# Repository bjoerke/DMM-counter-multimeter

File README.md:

# DMM-counter-multimeter
Impulszähler und Multimeter für das DMM-Board

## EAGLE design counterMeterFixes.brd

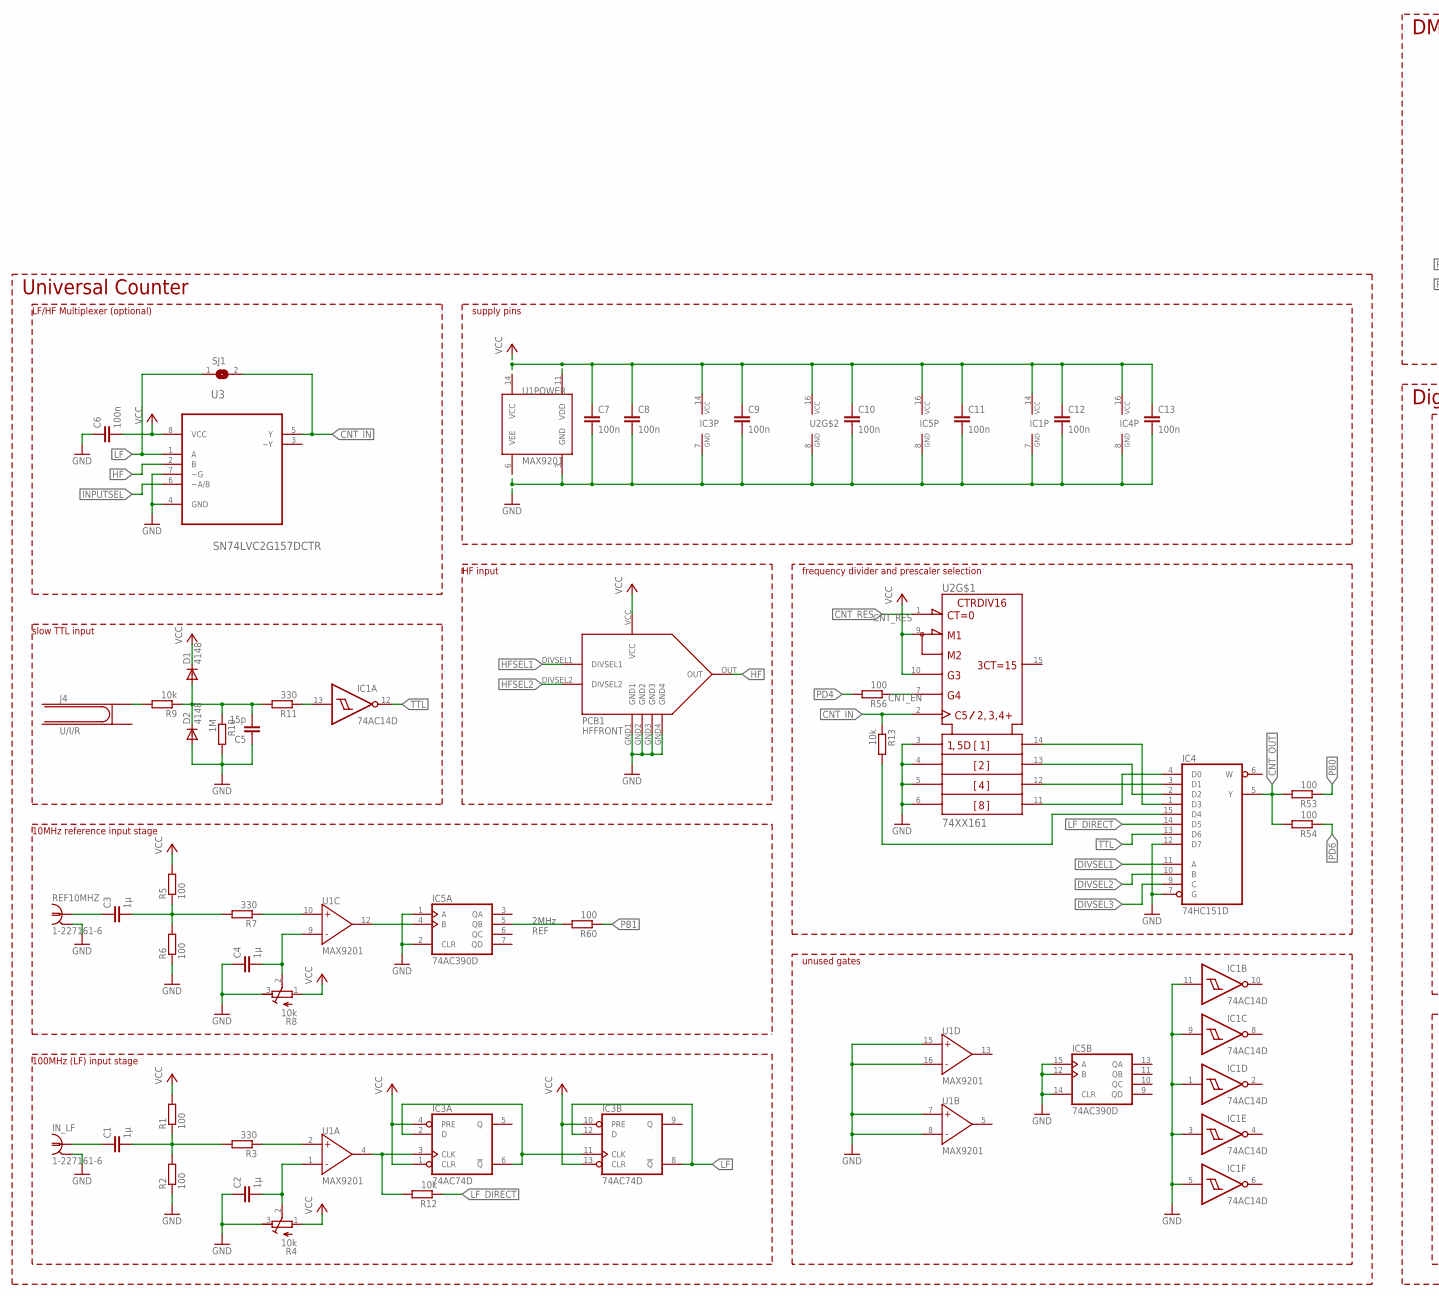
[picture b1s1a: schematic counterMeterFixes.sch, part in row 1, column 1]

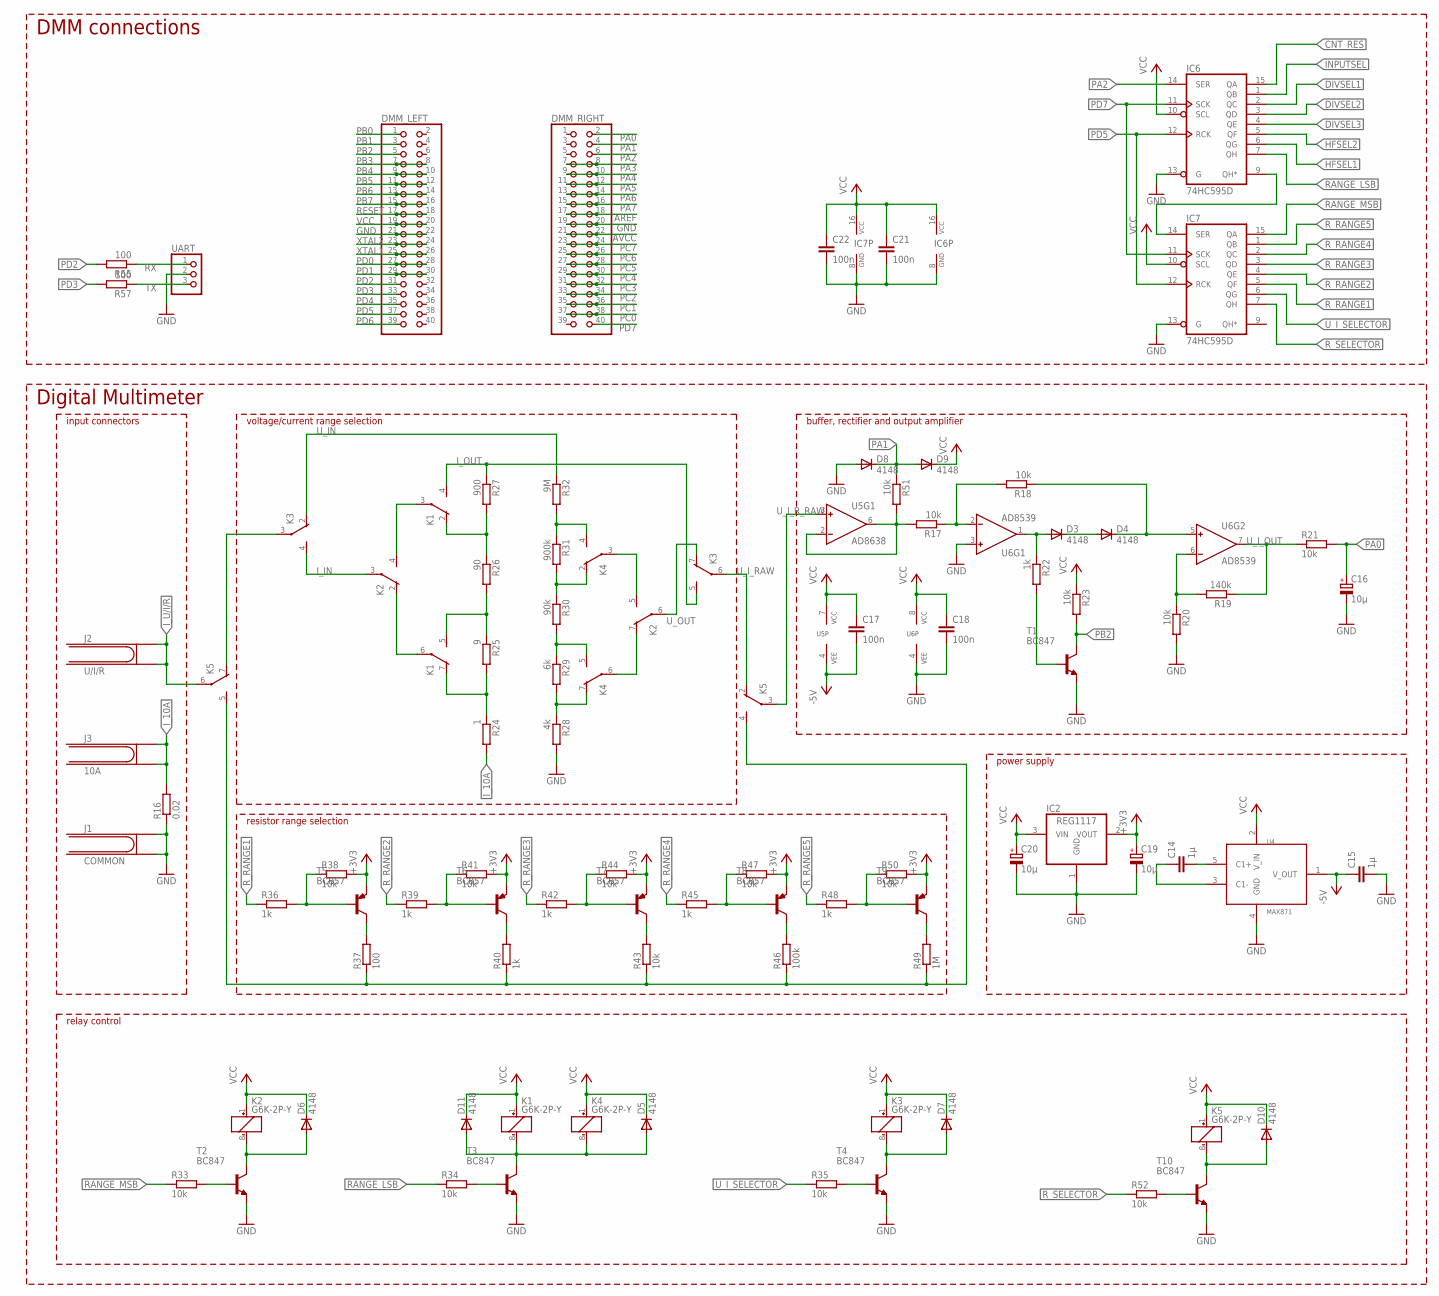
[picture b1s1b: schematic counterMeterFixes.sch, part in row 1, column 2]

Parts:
C1, C2, C3, C4, C14, C15: 1µ; C0603
C5: 15p; C0603
C6, C7, C8, C9, C10, C11, C12, C13, C17, C18, C21, C22: 100n; C0603
C16, C19, C20: 10µ; E2-5
D1, D2, D3, D4, D5, D6, D7, D8, D9, D10, D11: 4148; SOD323-W
DMM_LEFT: PINHD-2X20; 2X20
DMM_RIGHT: PINHD-2X20; 2X20
IC1: 74AC14D; SO14
IC2: REG1117; SOT223
IC3: 74AC74D; SO14
IC4: 74HC151D; SO16
IC5: 74AC390D; SO16
IC6, IC7: 74HC595D; SO16
IN_LF: 1-227161-6; AMP_227161
J1: COMMON; 4MMJACK
J2, J4: U/I/R; 4MMJACK
J3: 10A; 4MMJACK
K1, K2, K3, K4, K5: G6K-2P-Y
PCB1: HFFRONT
R1, R2, R5, R6, R37, R53, R54, R55, R56, R57, R60: 100; R0603
R3, R7, R11: 330; R0603
R4, R8: 10k; RTRIM64W
R9, R12, R13, R17, R18, R20, R21, R23, R33, R34, R35, R38, R41, R43, R44, R47, R50, R51, R52: 10k; R0603
R10, R49: 1M; R0603
R16: 0.02; R2512
R19: 140k; R0603
R22, R36, R39, R40, R42, R45, R48: 1k; R0603
R24: 1; R0603
R25: 9; R0603
R26: 90; R0603
R27: 900; R0603
R28: 4k; R0603
R29: 6k; R0603
R30: 90k; R0603
R31: 900k; R0603
R32: 9M; R0603
R46: 100k; R0603
REF10MHZ: 1-227161-6; AMP_227161
SJ1: SJ
T1, T2, T3, T4, T10: BC847; SOT23
T5, T6, T7, T8, T9: BC857; SOT23-BEC
U1: MAX9201; SOIC16
U2: 74XX161; SOIC16
U3: SN74LVC2G157DCTR; SOP65P400X130-8N
U4: MAX871; SOT23-5
U5: AD8638; SOIC8
U6: AD8539; SOIC8
UART: PINHD-1X3; 1X03

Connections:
+3V3: C19.+, IC2.2 (VOUT), R38.2, R41.2, R44.2, R47.2, R50.2, T5.E, T6.E, T7.E, T8.E, T9.E
-5V: C15.1, C17.2, U4.1 (V_OUT), U5.4 (VEE)
AREF: DMM_RIGHT.17, DMM_RIGHT.18
AVCC: DMM_RIGHT.21, DMM_RIGHT.22
CNT_EN: R56.1, U2.7 (ENP)
CNT_IN: R13.1, SJ1.2, U2.2 (CLK), U3.5 (Y)
CNT_IN_: IC4.15 (D4), R13.2
CNT_OUT: IC4.5 (Y), R53.2, R54.2
CNT_RES: IC6.15 (QA), U2.1 (!CLR)
DIVSEL1: IC4.11 (A), IC6.2 (QC)
DIVSEL2: IC4.10 (B), IC6.3 (QD)
DIVSEL3: IC4.9 (C), IC6.4 (QE)
GND: C2.1, C4.1, C5.1, C6.1, C7.2, C8.2, C9.2, C10.2, C11.2, C12.2, C13.2, C15.2, C16.-, C18.2, C19.-, C20.-, C21.2, C22.2, D2.A, D8.A, DMM_LEFT.21, DMM_LEFT.22, DMM_RIGHT.19, DMM_RIGHT.20, IC1.1 (I), IC1.3 (I), IC1.5 (I), IC1.7 (GND), IC1.9 (I), IC1.11 (I), IC2.1 (GND), IC3.7 (GND), IC4.7 (G), IC4.8 (GND), IC4.12 (D7), IC5.1 (A), IC5.2 (CLR), IC5.8 (GND), IC5.12 (B), IC5.14 (CLR), IC5.15 (A), IC6.8 (GND), IC6.13 (G), IC7.8 (GND), IC7.13 (G), IN_LF.2, J1.1@1 (1), J1.1@2 (2), PCB1.GND1, PCB1.GND2, PCB1.GND3, PCB1.GND4, R2.1, R4.3 (A), R6.1, R8.3 (A), R10.2, R16.1, R20.2, R28.2, REF10MHZ.2, T1.2 (E), T2.2 (E), T3.2 (E), T4.2 (E), T10.2 (E), U1.3 (GND), U1.6 (VEE), U1.7 (IN+), U1.8 (IN-), U1.15 (IN+), U1.16 (IN-), U2.3 (A), U2.4 (B), U2.5 (C), U2.6 (D), U2.8 (GND), U3.4 (GND), U3.7 (~G), U4.4 (GND), U6.3 (IN+), U6.4 (VEE), UART.2
HF: PCB1.OUT, U3.2 (B)
HFSEL1: IC6.6 (QG), PCB1.DIVSEL1
HFSEL2: IC6.5 (QF), PCB1.DIVSEL2
INPUTSEL: IC6.1 (QB), U3.6 (~A/B)
I_10A: J3.1@1 (1), J3.1@2 (2), R16.2, R24.2
I_IN: K2.3, K3.4 (S)
I_OUT: K1.4 (S), K3.5 (S), R27.1
I_U/I/R: J2.1@1 (1), J2.1@2 (2), K5.6
LF: IC3.8 (!Q), IC3.12 (D), SJ1.1, U3.1 (A)
LF_DIRECT: IC4.14 (D5), R12.1
LF_SIG: IC3.3 (CLK), R12.2, U1.4 (OUT)
unnamed: C2.2, R4.2 (S), U1.1 (IN-)
unnamed: R3.1, U1.2 (IN+)
unnamed: C1.2, R1.1, R2.2, R3.2
unnamed: C1.1, IN_LF.1
unnamed: C4.2, R8.2 (S), U1.9 (IN-)
unnamed: R7.1, U1.10 (IN+)
unnamed: C3.2, R5.1, R6.2, R7.2
unnamed: C3.1, REF10MHZ.1
unnamed: J4.1@1 (1), R9.2
unnamed: C5.2, D1.A, D2.C, R9.1, R10.1, R11.2
unnamed: IC1.13 (I), R11.1
unnamed: K4.7 (O), R28.1, R29.2
unnamed: IC5.4 (B), U1.12 (OUT)
unnamed: IC4.1 (D3), U2.14 (QA)
unnamed: K1.3, K2.4 (S)
unnamed: IC4.2 (D2), U2.13 (QB)
unnamed: IC4.3 (D1), U2.12 (QC)
unnamed: IC4.4 (D0), U2.11 (QD)
unnamed: C14.2, U4.5 (C1+)
unnamed: C14.1, U4.3 (C1-)
unnamed: D3.A, R22.1, U6.1 (OUT)
unnamed: D4.C, R18.1, U6.5 (IN+)
unnamed: R19.2, R20.1, U6.6 (IN-)
unnamed: IC6.9 (QH*), IC7.14 (SER)
unnamed: R17.1, R18.2, U6.2 (IN-)
unnamed: R17.2, R51.2, U5.2 (IN-), U5.6 (OUT)
unnamed: D3.C, D4.A
unnamed: R22.2, T1.1 (B)
unnamed: K1.7 (O), R24.1, R25.2
unnamed: K1.5 (S), R25.1, R26.2
unnamed: K1.2 (O), R26.1, R27.2
unnamed: K1.6, K2.2 (O)
unnamed: K4.5 (S), R29.1, R30.2
unnamed: K4.2 (O), R30.1, R31.2
unnamed: K4.4 (S), R31.1, R32.2
unnamed: K2.5 (S), K4.3
unnamed: K2.7 (O), K4.6
unnamed: D6.A, K2.8 (-), T2.3 (C)
unnamed: R33.2, T2.1 (B)
unnamed: D5.A, D11.A, K1.8 (-), K4.8 (-), T3.3 (C)
unnamed: R34.2, T3.1 (B)
unnamed: R35.2, T4.1 (B)
unnamed: D7.A, K3.8 (-), T4.3 (C)
unnamed: R36.2, R38.1, T5.B
unnamed: R37.2, T5.C
unnamed: K3.3, K5.7 (O)
unnamed: IC3.2 (D), IC3.6 (!Q), IC3.11 (CLK)
unnamed: R39.2, R41.1, T6.B
unnamed: R40.2, T6.C
unnamed: R42.2, R44.1, T7.B
unnamed: R43.2, T7.C
unnamed: R45.2, R47.1, T8.B
unnamed: R46.2, T8.C
unnamed: R48.2, R50.1, T9.B
unnamed: R49.2, T9.C
unnamed: K5.4 (S), K5.5 (S), R37.1, R40.1, R43.1, R46.1, R49.1
unnamed: R52.2, T10.1 (B)
unnamed: D10.A, K5.8 (-), T10.3 (C)
PA0: C16.+, DMM_RIGHT.2, R21.2
PA1: D8.C, D9.A, DMM_RIGHT.4, R51.1
PA2: DMM_RIGHT.6, IC6.14 (SER)
PA3: DMM_RIGHT.7, DMM_RIGHT.8
PA4: DMM_RIGHT.9, DMM_RIGHT.10
PA5: DMM_RIGHT.11, DMM_RIGHT.12
PA6: DMM_RIGHT.13, DMM_RIGHT.14
PA7: DMM_RIGHT.15, DMM_RIGHT.16
PB0: DMM_LEFT.1, R53.1
PB1: DMM_LEFT.3, R60.1
PB2: DMM_LEFT.5, R23.2, T1.3 (C)
PB3: DMM_LEFT.7, DMM_LEFT.8
PB4: DMM_LEFT.9, DMM_LEFT.10
PB5: DMM_LEFT.11, DMM_LEFT.12
PB6: DMM_LEFT.13, DMM_LEFT.14
PB7: DMM_LEFT.15, DMM_LEFT.16
PC0: DMM_RIGHT.37, DMM_RIGHT.38
PC1: DMM_RIGHT.35, DMM_RIGHT.36
PC2: DMM_RIGHT.33, DMM_RIGHT.34
PC3: DMM_RIGHT.31, DMM_RIGHT.32
PC4: DMM_RIGHT.29, DMM_RIGHT.30
PC5: DMM_RIGHT.27, DMM_RIGHT.28
PC6: DMM_RIGHT.25, DMM_RIGHT.26
PC7: DMM_RIGHT.23, DMM_RIGHT.24
PD0: DMM_LEFT.27, DMM_LEFT.28
PD1: DMM_LEFT.29, DMM_LEFT.30
PD2: DMM_LEFT.31, R55.2
PD3: DMM_LEFT.33, R57.2
PD4: DMM_LEFT.35, R56.2
PD5: DMM_LEFT.37, IC6.12 (RCK), IC7.12 (RCK)
PD6: DMM_LEFT.39, R54.1
PD7: DMM_RIGHT.40, IC6.11 (SCK), IC7.11 (SCK)
RANGE_LSB: IC6.7 (QH), R34.1
RANGE_MSB: IC7.15 (QA), R33.1
REF: IC5.5 (QB), R60.2
RESET: DMM_LEFT.17, DMM_LEFT.18
RX: R55.1, UART.1
R_RANGE1: IC7.5 (QF), R36.1
R_RANGE2: IC7.4 (QE), R39.1
R_RANGE3: IC7.3 (QD), R42.1
R_RANGE4: IC7.2 (QC), R45.1
R_RANGE5: IC7.1 (QB), R48.1
R_SELECTOR: IC7.7 (QH), R52.1
TTL: IC1.12 (O), IC4.13 (D6)
TX: R57.1, UART.3
U_IN: K3.2 (O), R32.1
U_I_OUT: R19.1, R21.1, U6.7 (OUT)
U_I_RAW: K3.6, K5.2 (O)
U_I_R_RAW: K5.3, U5.3 (IN+)
U_I_SELECTOR: IC7.6 (QG), R35.1
U_OUT: K2.6, K3.7 (O)
VCC: C6.2, C7.1, C8.1, C9.1, C10.1, C11.1, C12.1, C13.1, C17.1, C18.1, C20.+, C21.1, C22.1, D1.C, D5.C, D6.C, D7.C, D9.C, D10.C, D11.C, DMM_LEFT.19, DMM_LEFT.20, IC1.14 (VCC), IC2.3 (VIN), IC3.1 (CLR), IC3.4 (PRE), IC3.10 (PRE), IC3.13 (CLR), IC3.14 (VCC), IC4.16 (VCC), IC5.16 (VCC), IC6.10 (SCL), IC6.16 (VCC), IC7.10 (SCL), IC7.16 (VCC), K1.1 (+), K2.1 (+), K3.1 (+), K4.1 (+), K5.1 (+), PCB1.VCC, R1.2, R4.1 (E), R5.2, R8.1 (E), R23.1, U1.11 (VDD), U1.14 (VCC), U2.9 (!LOAD), U2.10 (ENT), U2.16 (VCC), U3.8 (VCC), U4.2 (V_IN), U5.7 (VCC), U6.8 (VCC)
XTAL1: DMM_LEFT.25, DMM_LEFT.26
XTAL2: DMM_LEFT.23, DMM_LEFT.24

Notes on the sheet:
10MHz reference input stage
HF input
slow TTL input
100MHz (LF) input stage
LF/HF Multiplexer (optional)
2MHz
supply pins
frequency divider and prescaler selection
unused gates
Universal Counter
relay control
resistor range selection
voltage/current range selection
buffer, rectifier and output amplifier
input connectors
power supply
Digital Multimeter
DMM connections

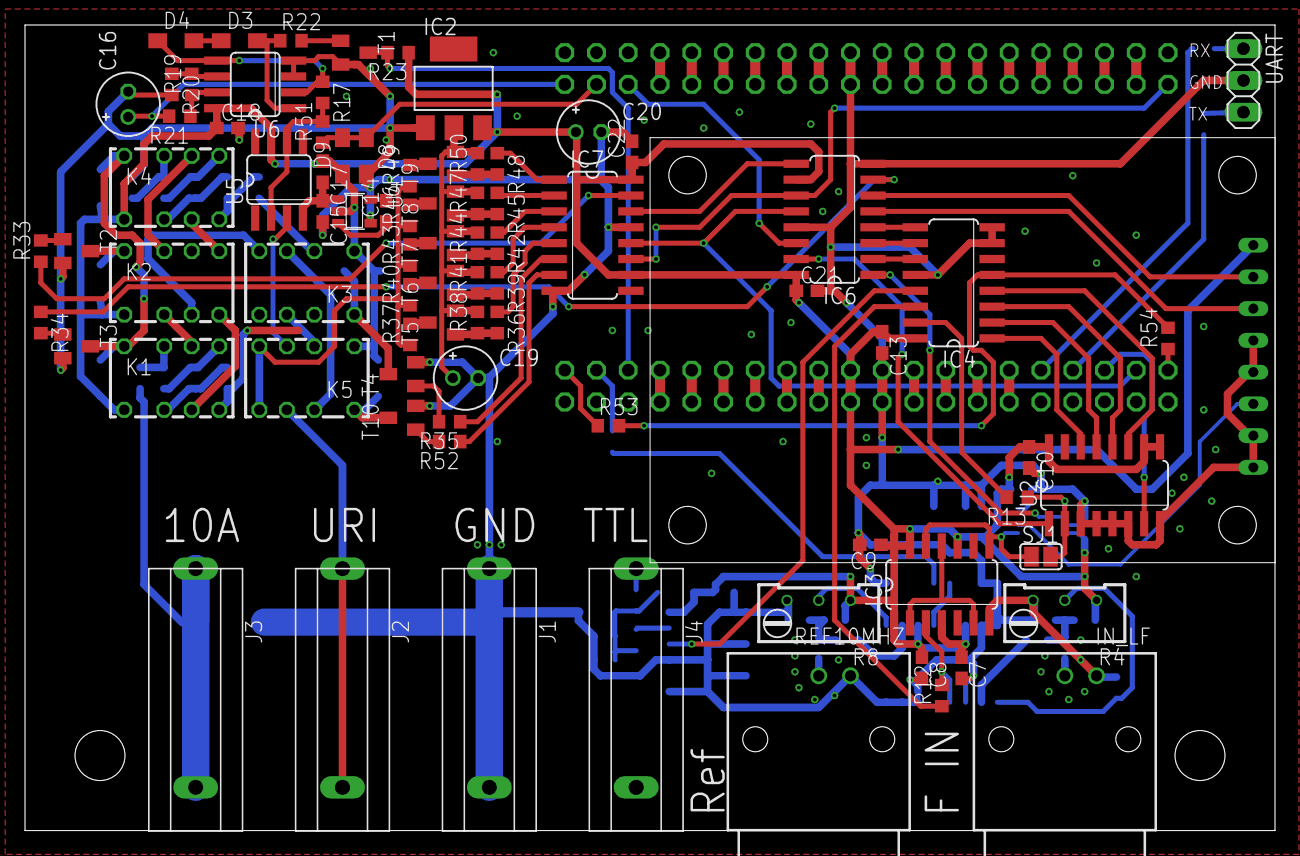
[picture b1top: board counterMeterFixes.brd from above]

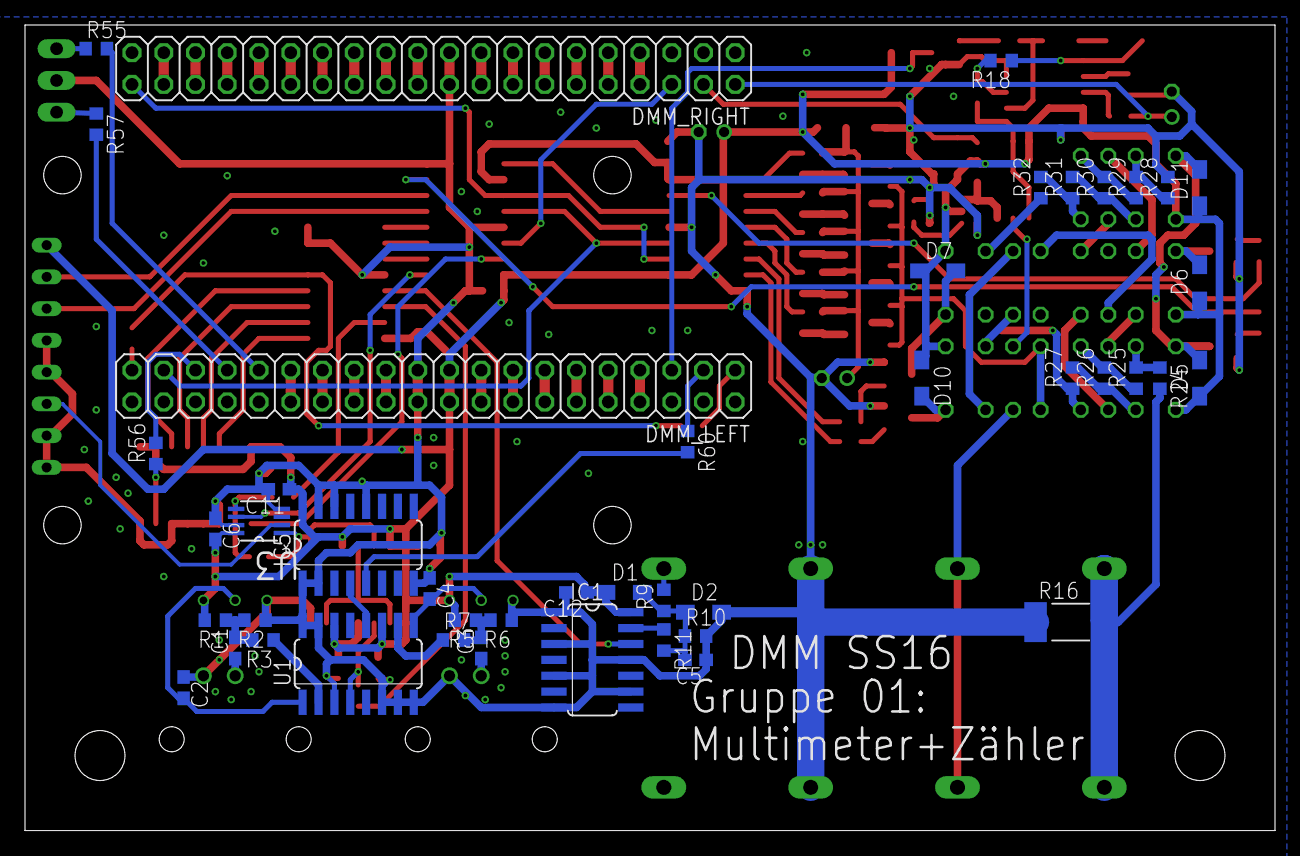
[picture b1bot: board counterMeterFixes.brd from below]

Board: 2 copper layers, 100.0 x 64.4 mm, 128 parts (45 on the bottom side), 136 nets.

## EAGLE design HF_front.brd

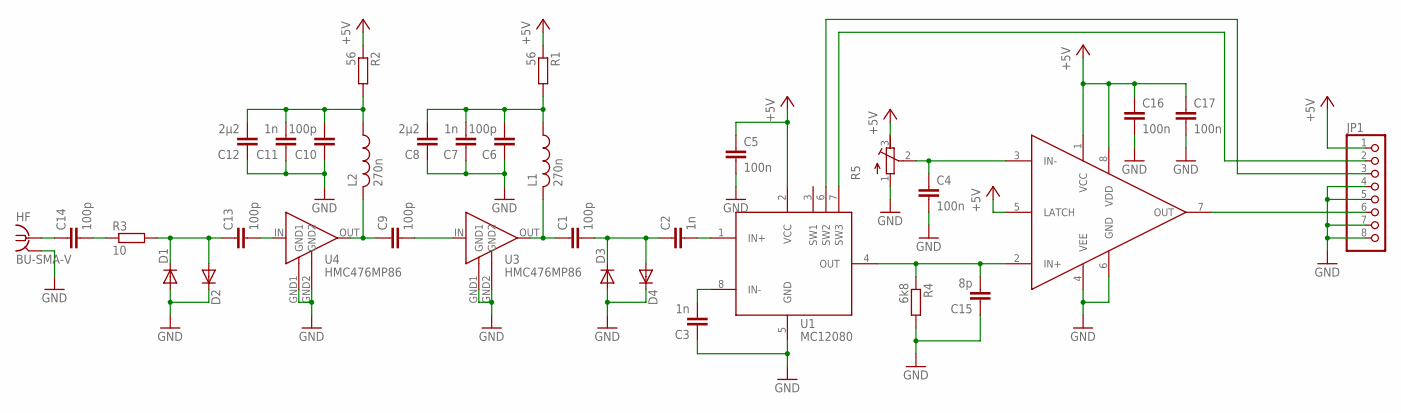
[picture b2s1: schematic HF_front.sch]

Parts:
C1, C6, C9, C10, C13, C14: 100p; C0603
C2, C3, C7, C11: 1n; C0603
C4, C5, C16, C17: 100n; C0603
C8, C12: 2µ2; C0603
C15: 8p; C0603
D1, D2, D3, D4: DIODE-SOD323-W; SOD323-W
HF: BU-SMA-V
JP1: PINHD-1X8; 1X08
L1, L2: 270n; R0603
R1, R2: 56; R0603
R3: 10; R0603
R4: 6k8; R0603
R5: R-TRIMM64W; RTRIM64W
U1: MC12080; SOIC8
U2: MAX9203; SOIC8
U3, U4: HMC476MP86; MICRO-X

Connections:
+5V: C5.1, C16.1, C17.1, JP1.1, R1.1, R2.1, R5.3 (A), U1.2 (VCC), U2.1 (VCC), U2.5 (LATCH), U2.8 (VDD)
GND: C3.1, C4.2, C5.2, C6.1, C7.1, C8.1, C10.1, C11.1, C12.1, C15.1, C16.2, C17.2, D1.A, D2.C, D3.A, D4.C, HF.2, HF.3 (2), HF.4 (2), HF.5 (2), JP1.4, JP1.5, JP1.7, JP1.8, R4.2, R5.1 (E), U1.5 (GND), U2.4 (VEE), U2.6 (GND), U3.GND1, U3.GND2, U4.GND1, U4.GND2
unnamed: C6.2, C7.2, C8.2, L1.1, R1.2
unnamed: C1.1, L1.2, U3.OUT
unnamed: C10.2, C11.2, C12.2, L2.1, R2.2
unnamed: C9.1, L2.2, U4.OUT
unnamed: C9.2, U3.IN
unnamed: C2.2, U1.1 (IN+)
unnamed: C3.2, U1.8 (IN-)
unnamed: C15.2, R4.1, U1.4 (OUT), U2.2 (IN+)
unnamed: C4.1, R5.2 (S), U2.3 (IN-)
unnamed: C14.1, HF.1
unnamed: C14.2, R3.1
unnamed: C13.1, D1.C, D2.A, R3.2
unnamed: C13.2, U4.IN
unnamed: C1.2, C2.1, D3.C, D4.A
unnamed: JP1.6, U2.7 (OUT)
unnamed: JP1.2, U1.7 (SW3)
unnamed: JP1.3, U1.6 (SW2)

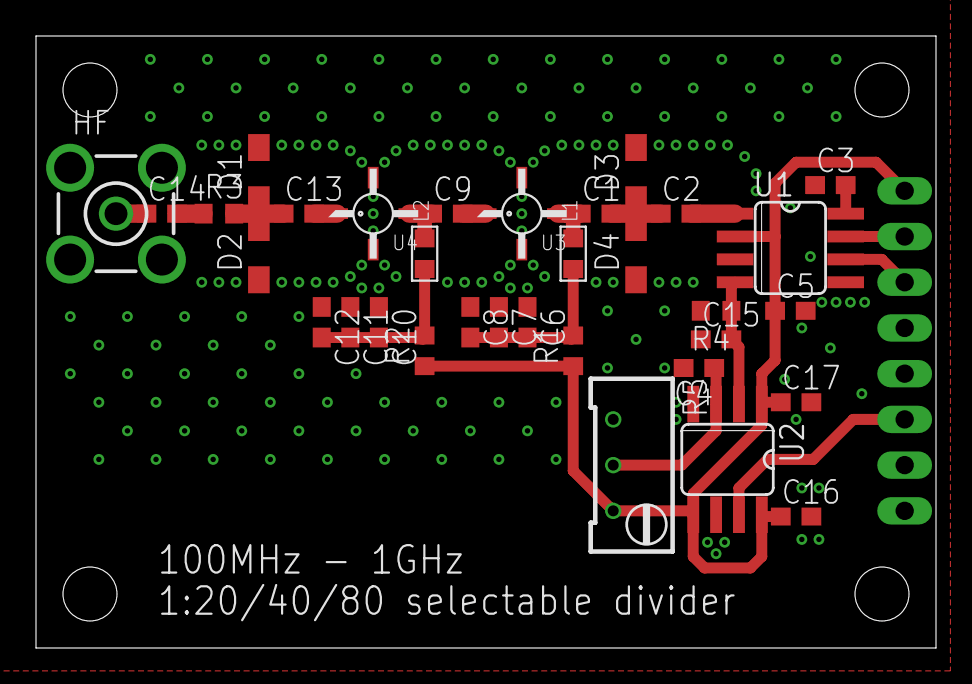
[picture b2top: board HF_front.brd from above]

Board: 2 copper layers, 50.0 x 34.0 mm, 34 parts (1 on the bottom side), 19 nets.

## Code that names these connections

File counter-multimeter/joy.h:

#ifndef _JOY_H_
#define _JOY_H_

#include <avr/io.h>
#include <avr/interrupt.h>
#include <stdint.h>
#include <stdlib.h>
#include <util/delay.h>
#include <avr/pgmspace.h>
#include <avr/wdt.h>

#include "systime.h"
#include "gui.h"

#define JOY_PIN			PINA
#define JOY_DDR			DDRA
#define JOY_PORT		PORTA

#define JOY_UP_PIN		PA7
#define JOY_RIGHT_PIN 	PA4
#define JOY_DOWN_PIN	PA6
#define JOY_LEFT_PIN	PA5
#define JOY_PUSH_PIN	PA3

#define JOY_MASK 		((1<<JOY_UP_PIN)|(1<<JOY_RIGHT_PIN)|(1<<JOY_DOWN_PIN)|(1<<JOY_LEFT_PIN)|(1<<JOY_PUSH_PIN))

#define JOY_UP			0x80
#define JOY_RIGHT		0x10
#define JOY_DOWN		0x40
#define JOY_LEFT		0x20
#define JOY_PUSH		0x08

struct {
	uint8_t state;
	uint8_t pressed;
} joy;

/**
 * \brief Initializes joystick
 */
void joy_Init(void);

/**
 * \brief Reports if a joystick button has been pressed
 *
 * Each press is only reported once.
 *
 * \param joymask Joystick button that will be checked.
 * \return Mask of pressed buttons
 */
uint8_t joy_Pressed(uint8_t joymask);

/**
 * \brief Reports if a joystick button is currently pressed
 *
 * \param joymask Joystick button that will be checked.
 * \return Mask of pressed buttons
 */
uint8_t joy_State(uint8_t joymask);

/**
 *  \brief Reads joystick pins, debounces and writes new state
 *
 *  see: https://www.mikrocontroller.net/articles/Entprellung
 */
void joy_Update(void);

#endif

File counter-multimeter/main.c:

#ifndef F_CPU
#define F_CPU 16000000UL
#endif

#include <avr/io.h>
#include <avr/interrupt.h>
#include <stdint.h>
#include <stdlib.h>
#include <avr/pgmspace.h>

#include "uartProtocol.h"
#include "includes/lcd.h"
#include "includes/twi.h"
#include "multimeter.h"
#include "systime.h"
#include "counterHAL.h"
#include "gui.h"
#include "joy.h"

int main(void) {
	//// set PB0-PB3 as output
	//DDRB = 0x0F;
	//// set PB0-PB3 on high-level (internal Pull-Up on)
	//PORTB |= 0x0F;		// Required for DMM Board DMM Board 2013

	// set PB0, PB1, PB3 as output
	DDRB = 0x0B;		// 1011
	// set PB0, PB1, PB3 on high-level (internal Pull-Up on)
	PORTB |= 0x0B;		// Required for DMM Board DMM Board 2013
	// set PB2 as input
	DDRB &= ~(1 << PINB2);
	// set PB2 on high-level (internal Pull-Up on)
	PORTB |= (1 << PINB2);

	LCD_Init();
	uartProtocol_Init();

	time_Init();
	joy_Init();
	shift_Init();
	counter_Init();
	ADC_Init();

	Backlight_LED(BL_BLUE_ON | BL_GREEN_ON | BL_RED_ON);

	LCD_Clear();
/*	LCD_PutString_P(PSTR("	                   \r\n"));
	LCD_PutString_P(PSTR("	                   \r\n"));
	LCD_PutString_P(PSTR("    Willkommen zur   \r\n"));
	LCD_PutString_P(PSTR("     Demo-Version    \r\n"));
	LCD_PutString_P(PSTR("         des         \r\n"));
	LCD_PutString_P(PSTR("    Counter-Meters   \r\n"));
	LCD_PutString_P(PSTR("                     \r\n"));
	LCD_PutString_P(PSTR("                     \r\n")); */
	LCD_Update();
	//time_Waitms(3000);

	// Enable interrupts:
	sei();

/*
    //UART protocol ussage
	uint8_t i=0;
	while(1) {
		request* request = 
		uartProtocol_WaitRequest();
		LCD_PutString("#");
		LCD_Update();
		response response;
		response.direct_voltage.range = i;
		response.direct_voltage.value = 0;
		uartProtocol_SendResponse(&response);
		i++;
	} 
*/
	
	while (1) {
		gui_DisplayMainMenu();
		time_Waitms(100);
		if (gui.selectedEntry < GUI_NUM_MEASUREMENT_ENTRIES
				&& gui.measurementActive) {
			gui_TakeMeasurement();
		} else {
			time.beep = 0;
			DMM_SetDefault();
			Backlight_LED(BL_BLUE_ON | BL_GREEN_ON | BL_RED_ON);
		}
		gui_HandleUserInput();
	}
}

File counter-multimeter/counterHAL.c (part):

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
void counter_Init(void) {
	// reference gate enable pin (OC1B)
	DDRD |= (1 << PD4);
	// input capture pin (ICP1)
	DDRD &= ~(1 << PD6);
	PORTD |= (1 << PD6);
	// signal and reference counter pins
	DDRB &= ~((1 << PB0) | (1 << PB1));
	// enable pull-ups
	PORTB |= (1 << PB0) | (1 << PB1);

	shift_Clear(CNT_RESET_SHIFT);
//    shift_Set(CNT_HFSEL1_SHIFT);
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	TCCR1A &= ~((1 << COM1B1) | (1 << COM1B0));
	TIMSK1 &= ~(1 << OCIE1B);

	// at this point OC1B (PD4) has been high for exactly ticks*(1/2MHz) seconds
	/*****************************************************************
	 * Step 3:  Calculate counted signal impulses
	 ****************************************************************/
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	}
#else
	// enable counter chip
	PORTD |= (1<<PD4);
	// setup input capture functionality at ICP3
	// start with rising edge
	TCCR1B |= (1 << ICES1);
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			&& (starttime + timeout > time_Getms()))
		;
	// disable counter chip
	PORTD &= ~(1<<PD4);
	TIMSK1 &= ~(1 << ICIE1);
	if (counter.sigGateStatus != CNT_GATE_CLOSED) {
		// timeout has occured
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
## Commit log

2016-04-26 Added simple signal generator
2016-04-27 Changed title of repository
2016-04-28 first draw of the schematic
2016-04-28 optional HF frontend board
2016-05-01 some pin changes in schematic + first draw of the PCB layout
2016-05-01 schematic as pdf
2016-05-01 some low level drivers for the counter part
2016-05-01 very basic counter test/example
2016-05-02 some input protection + buffer output filter
2016-05-02 more minor pcb changes
2016-05-02 partlist counterMeter
2016-05-02 updated pdf schematic
2016-05-02 Updated partlist
    Updated and changed the partlist to the requested format.
2016-05-02 added simulation feature (debugging just with the DMM board possible)
2016-05-02 counter testing enabled
2016-05-03 tiny layout correction
2016-05-03 Gerber files for PCB production
2016-05-09 corrected a link and erased column
2016-05-16 Again an update of the partlist
2016-05-24 Bugfix: forgot shift of shift register content. Plus stretching the clock pulses slightly
2016-05-24 Multimeter HAL: selecting measurement ranges
2016-05-24 relay contacts 5 and 7 on K3 swapped
2016-05-24 corrected frequency division of reference signal IC5A Pin 6 instead of 5
2016-05-27 rename counter->counterHAL
2016-05-29 Added Makefile and .gitignorewq
2016-06-01 Added Atmel Studio project files to .gitignore
2016-06-01 First UART test
2016-06-01 Added listener to uart driver
2016-06-01 UART Protocol stub
2016-06-02 Added checksum generator
2016-06-02 Removed object files from git
2016-06-02 Moved schematics to seperate folder
2016-06-08 Added new files necessary for the GUI
    Adapted and modified from the old project "Multimeter" (summer term 2015)
2016-06-08 Updated the main.c
    Hopefully merged both while-loops correctly. Additionally added a new function.
2016-06-10 refclk define + renameing include guard
2016-06-10 added selected input to cnt struct + commented all HF related code
2016-06-10 added macros to increment/decrement prescalers
2016-06-10 higher level counter functions (untested)
2016-06-11 wait for fifo ready in UART_PutChar + UART_PutLongInteger added
2016-06-11 inttype change in counter simulation functions
2016-06-11 Debug messages included (commented)
2016-06-11 maximum sample time limited + maximum capture frequency
2016-06-12 duty cycle measurement function added
2016-06-14 Prepared the multimeter for ADC. Init in main.
2016-06-15 ADC fixes
2016-06-15 test measurement modes for testing the multimeter hardware
2016-06-15 lcd put integer function
2016-06-16 bug fixes (interrupt flag + overflows)
2016-06-16 more bugfixes (reduced maximum input frequency, overflow) + debug msgs
2016-06-16 counter test application
2016-06-16 allow timer callback registration (10ms), will be used for debouncing
2016-06-16 proper joystick debounce function (old joystick routine partially kept)
2016-06-17 include guards added
2016-06-17 added secondary (bigger) font
    It does cost a lot of program memory but hey: we've got 128kB of it!
2016-06-17 new GUI
2016-06-17 delay in main menu loop to slow display down
2016-06-18 moved main menu loop into main + added settings menu
2016-06-22 GUI prototype
2016-06-23 Included some new multimeter-functions
2016-06-23 removed unnecessary function 'do_measure'
2016-06-23 Included Auto-Range-Measuring
2016-06-24 defined PINB2 as input
2016-06-24 included sign-evaluation and continuity-mode
2016-06-24 Application for testing the uart protocol
2016-06-24 Removed checksum generator
2016-07-01 removed deprecated functions
2016-07-01 Autorange borders moved -> got rid of oscillation between ranges
2016-07-01 reduced some redundancies in the multimeter code + new GUI things
    Multimeter:
    - Redundancies reduced in voltage, current and resistance measurement
    - Continuity measurement fixed on 2kOhm range
    - Display color changes in continuity mode
    GUI:
    - display selected range in auto mode on top of screen
2016-07-01 now with real beep ;)
2016-07-01 bugfix: ranges on I-mode didn't change
2016-07-01 gitignore eclipse
2016-07-02 display correct units + improvement on resistance auto ranging
2016-07-02 only evaluate sign in DC mode + included form factor in AC mode
2016-07-02 safe mode implemented
2016-07-03 Finished uart protocol
2016-07-05 bugfix counter: indirect method only worked with prescaler 1 and 4
2016-07-05 included calculation of the adc-mean
    see function adc_get()
2016-07-06 Changed uart protocol
2016-07-06 Serial IO for unix
2016-07-06 Added binary for linux
2016-07-06 Added binary for windows
2016-07-06 Binaries for win32
2016-07-07 optional timeout on uartProtocol_WaitRequest
2016-07-07 counter range param now pointer -> contains selected range on autoranging
2016-07-07 Basic uart protocol integration
2016-07-07 bugfix: used reference instead of value
2016-07-07 more precise results without hardware-divider
2016-07-07 Uart-protocol integrated (not fully tested yet)
2016-07-07 Minor bug fixes for uart-tester
2016-07-07 Adapted protocol for negative values (uint32_t -> int32_t)
2016-07-07 increased maximum pin frequency -> faster results
2016-07-11 Win32 binariy

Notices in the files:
parts and their libraries:
xmaker: Licensing: CC v3.0 Attribution-Share Alike
http://creativecommons.org/licenses/by-sa/3.0
